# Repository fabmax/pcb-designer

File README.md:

# PCB Designer

A schematic, PCB and part editor written in Rust (egui + wgpu). Schematic changes show up on
the board immediately, projects are folders of JSON files that diff well, and AI agents can
work on the open project through MCP while you watch.

- **Schematic:** hierarchical sheets, buses, labels and power ports as in KiCad, live ERC.
- **PCB:** push-and-shove routing, net classes, blind and buried vias, copper zones,
  keepouts, DRC.
- **Libraries:** a built-in library of generic parts, symbol, footprint and part editors,
  KiCad library and project import, KiCad project export.
- **Manufacturing:** Gerber X2, Excellon, job file, BOM and positions (JLCPCB, PCBWay), a
  Gerber viewer, schematic PDF.
- **Simulation:** ngspice with probes on the schematic, plots, measurements, a tuner and
  parameter sweeps.
- **Agents:** an MCP server in the app or headless; every edit an agent makes can be
  undone.

The [audio amplifier example](docs/user-interface.md#example-projects) (`--example amp`):
schematic, board, and the spectrum of a 1 kHz sine through it.

## Documentation

- [User interface and settings](docs/user-interface.md)
- [Schematic](docs/schematic.md)
- [PCB](docs/pcb.md)
- [Editing](docs/editing.md)
- [Design checks (ERC and DRC)](docs/checks.md)
- [Libraries and parts](docs/libraries.md)
- [Manufacturing files](docs/manufacturing.md)
- [Simulation](docs/simulation.md)
- [KiCad import and export](docs/kicad.md)
- [Agents (MCP)](docs/agents.md)
- [Command line](docs/command-line.md)
- [Development](docs/development.md)

## Install

Download the build for your system from the
[releases](https://github.com/fabmax/pcb-designer/releases): macOS (Apple Silicon),
Linux and Windows (x86_64).

- **macOS:** unzip and move `PCB Designer.app` to Applications. The app is only ad-hoc
  signed (not notarized), so macOS refuses to open it at first: open it once, then click
  **Open Anyway** in **System Settings → Privacy & Security** and confirm. (Right-click →
  Open no longer does this since macOS 15.) Or clear the download's quarantine flag with
  `xattr -dr com.apple.quarantine "PCB Designer.app"`.
- **Linux:** unpack `pcb-designer` from the archive and run it.
- **Windows:** unzip and run `pcb-designer.exe`.

[ngspice](https://ngspice.sourceforge.io/) comes with the app for simulation.

Or try it in the browser, without installing: [fabmax.github.io/pcb-designer/](https://fabmax.github.io/pcb-designer/)
(experimental; needs WebGPU, see [the browser version](docs/web.md)).

## Build from source

With a current stable [Rust](https://rustup.rs):

```sh
cargo run --release -p app                 # an empty project
cargo run --release -p app -- my-board     # open a project folder
cargo run --release -p app -- --demo       # the demo project
cargo run --release -p app -- --example amp  # a discrete audio amplifier
cargo test --workspace
```

On Linux, install the window system's development packages first. For simulation,
`scripts/build-ngspice.sh` builds the ngspice the app bundles; on macOS,
`scripts/bundle-macos.sh` builds the app bundle. See [Development](docs/development.md).

## License

PCB Designer is licensed under the [MIT License](LICENSE). Bundled third-party assets keep
their own licenses: [JetBrains Mono](https://www.jetbrains.com/lp/mono/) under the SIL Open
Font License 1.1 (`crates/render/fonts/OFL.txt`), [Tabler icons](https://tabler.io/icons)
under MIT (`crates/app/icons/tabler/LICENSE`), [ngspice](https://ngspice.sourceforge.io/)
under its own licenses (mainly BSD; its COPYING ships with it). KiCad's libraries, which the app can
download, are CC-BY-SA 4.0 with an exception for designs made with them.

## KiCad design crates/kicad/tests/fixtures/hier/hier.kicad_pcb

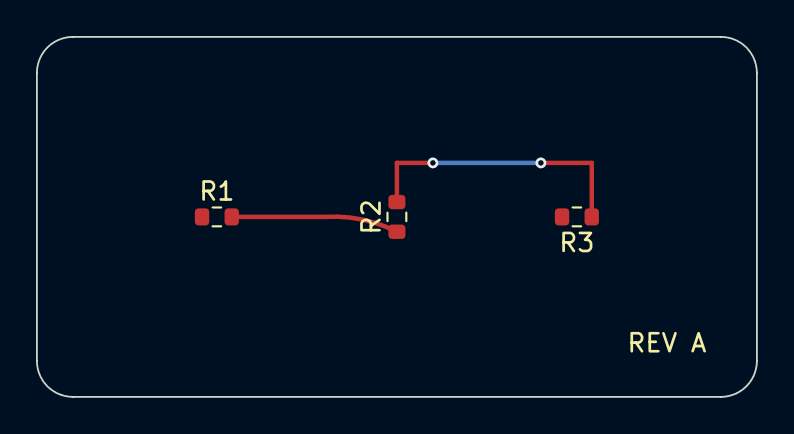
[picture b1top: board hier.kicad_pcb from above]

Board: 2 copper layers, 40.0 x 20.0 mm, 3 parts (0 on the bottom side), 2 nets.

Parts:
R1, R2: 10k; R_0603_1608Metric
R3: 1k; R_0603_1608Metric

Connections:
/amp/OUT: R1.2, R2.1
unnamed: R2.2, R3.1
